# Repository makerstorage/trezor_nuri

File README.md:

# trezor_nuri
I slightly change the trezor one hw (https://github.com/trezor/trezor-hardware/tree/master/electronics/trezor_one) in order to solder the components easily. I use 0805 package components. This design can be more popular for the maker community. I also watch this video (https://www.youtube.com/watch?v=mZmv4wG6_PE) and do not use the resistors that are not populated also on the original trezor one. Unfortunately I can not make my design work :( 
I saw that all the voltage points have 3v. I am not expert but I try to upload the demo code and as well as the firmware as described here (https://mcudev.github.io/trezor-dev-kit/) I can upload the bin files without problem. The STlink v2 also finds the STM32 IC.
I am looking for help from the experts. I am here to try your all suggestions.

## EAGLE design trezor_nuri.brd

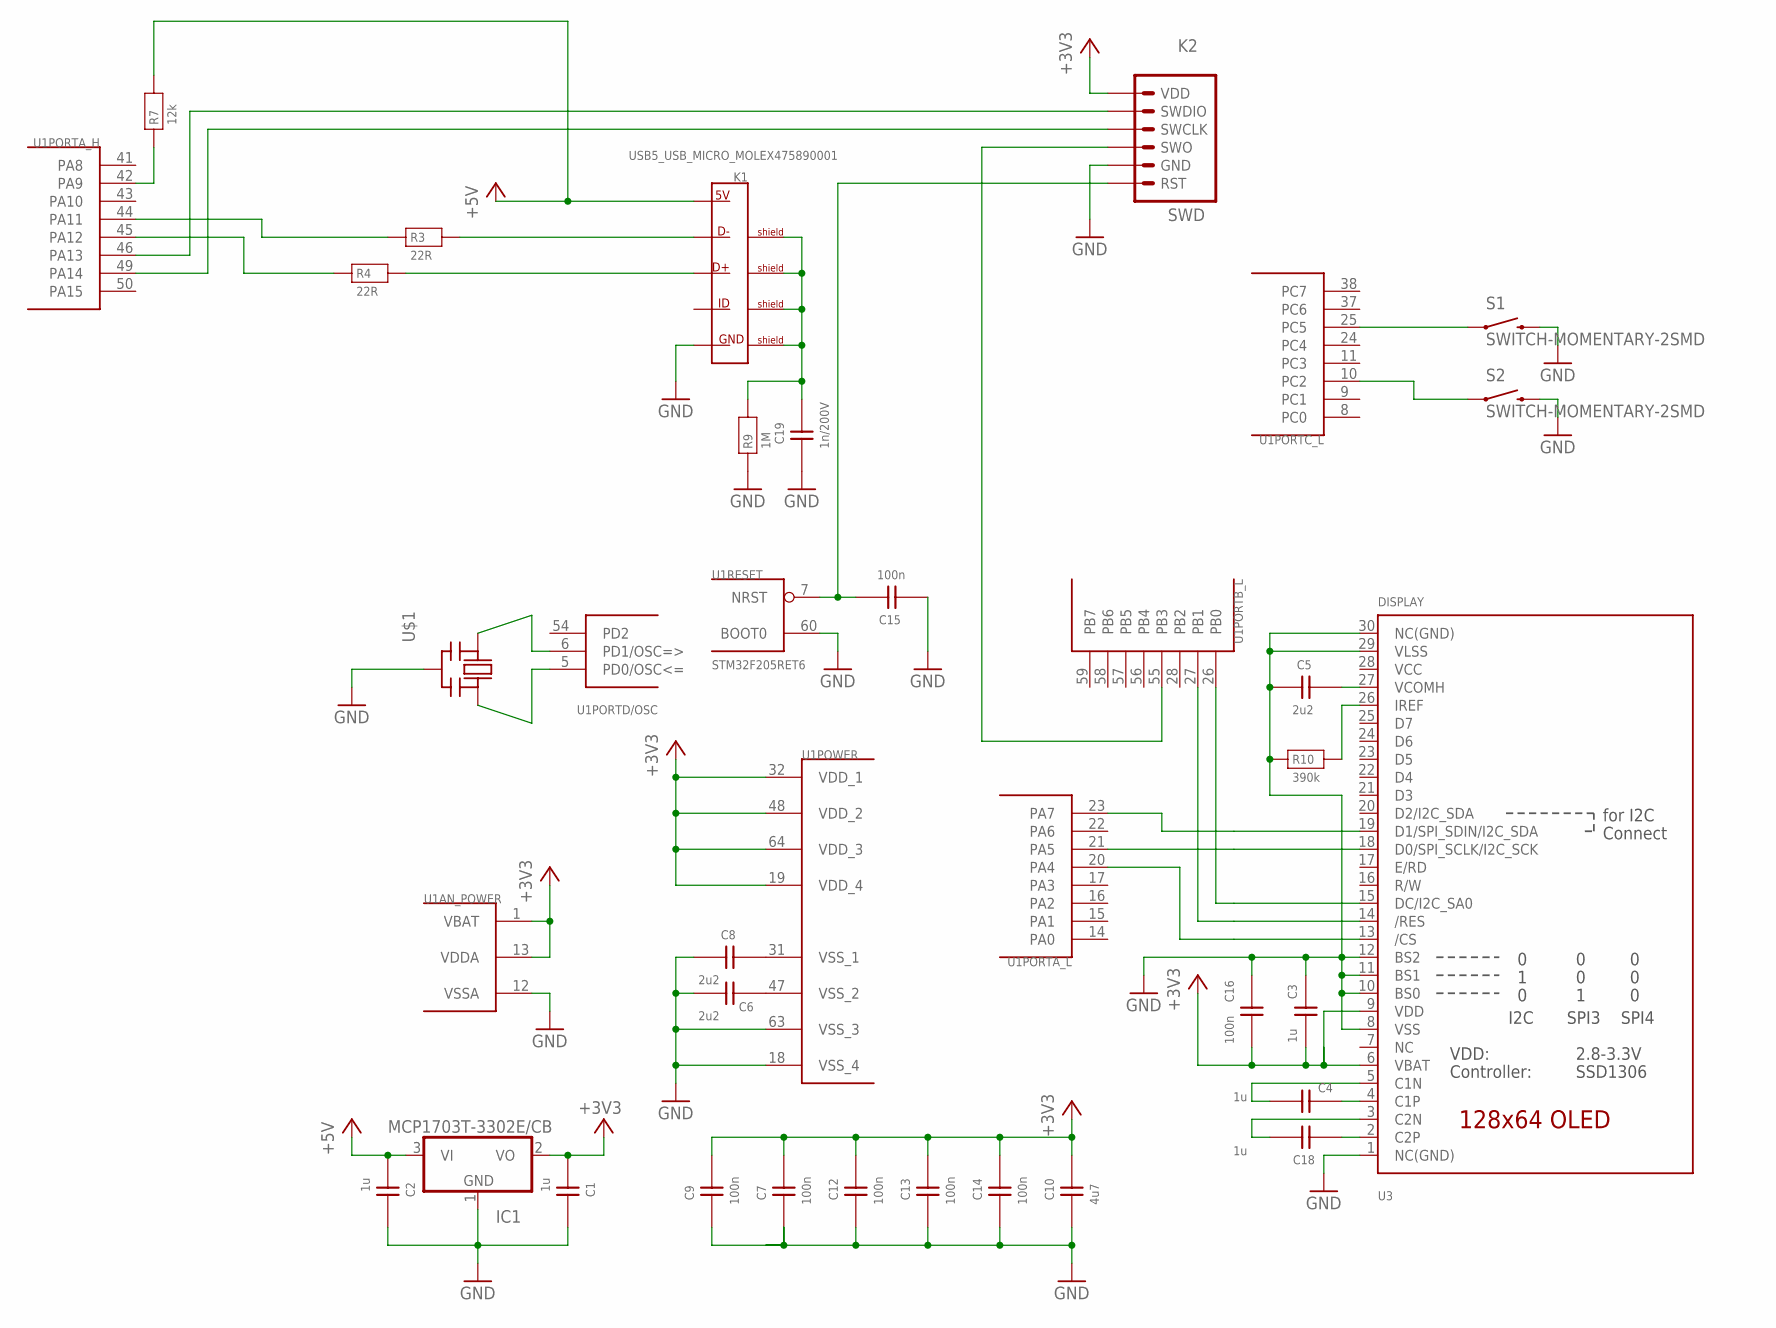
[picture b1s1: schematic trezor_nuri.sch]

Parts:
C1, C2, C3, C4, C18: 1u; 0805
C5, C6, C8: 2u2; 0805
C7, C9, C12, C13, C14, C15, C16: 100n; 0805
C10: 4u7; 0805
C19: 1n/200V; 0805
IC1: MCP1703T-3302E/CB; SOT23
K1: USB5_USB_MICRO_MOLEX475890001; USB_MICRO-MOLEX475890001
K2: SWD
R3, R4: 22R; 0805
R7: 12k; 0805
R9: 1M; 0805
R10: 390k; 0805
S1, S2: SWITCH-MOMENTARY-2SMD; TACTILE_SWITCH_SMD
U1: STM32F205RET6; TQFP64
U3: DISPLAY; UG-2864HSWEG01_0.96IN_WRAPAROUND
U$1: CERMOSCILL-CSTCRG; CSTCR-G

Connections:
+3V3: C1.1, C3.1, C7.2, C9.2, C10.2, C12.2, C13.2, C14.2, C16.1, IC1.2 (VO), K2.6 (VDD), U1.1 (VBAT), U1.13 (VDDA), U1.19 (VDD_4), U1.32 (VDD_1), U1.48 (VDD_2), U1.64 (VDD_3), U3.6 (VBAT), U3.9 (VDD)
+5V: C2.1, IC1.3 (VI), K1.1 (1_5V), R7.2
GND: C1.2, C2.2, C3.2, C5.1, C6.1, C7.1, C8.1, C9.1, C10.1, C12.1, C13.1, C14.1, C15.1, C16.2, C19.1, IC1.1 (GND), K1.5 (5_GND), K2.2 (GND), R9.1, R10.1, S1.3 (2), S1.4 (2), S2.3 (2), S2.4 (2), U1.12 (VSSA), U1.18 (VSS_4), U1.60 (BOOT0), U1.63 (VSS_3), U3.1 (NC(GND)), U3.8 (VSS), U3.10 (BS0), U3.11 (BS1), U3.12 (BS2), U3.29 (VLSS), U3.30 (NC(GND)), U$1.2 (GND)
unnamed: U1.23 (PA7), U3.19 (D1/SPI_SDIN/I2C_SDA)
unnamed: C15.2, K2.1 (RST), U1.7 (NRST)
unnamed: U1.26 (PB0), U3.15 (DC/I2C_SA0)
unnamed: C8.2, U1.31 (VSS_1)
unnamed: U1.21 (PA5), U3.18 (D0/SPI_SCLK/I2C_SCK)
unnamed: C5.2, U3.27 (VCOMH)
unnamed: U1.27 (PB1), U3.14 (/RES)
unnamed: C6.2, U1.47 (VSS_2)
unnamed: R10.2, U3.26 (IREF)
unnamed: C18.1, U3.2 (C2P)
unnamed: C4.1, U3.4 (C1P)
unnamed: C18.2, U3.3 (C2N)
unnamed: C4.2, U3.5 (C1N)
unnamed: K2.3 (SWO), U1.55 (PB3)
unnamed: K2.5 (SWDIO), U1.46 (PA13)
unnamed: U1.20 (PA4), U3.13 (/CS)
unnamed: K2.4 (SWCLK), U1.49 (PA14)
unnamed: R3.1, U1.44 (PA11)
unnamed: S1.1, S1.2 (1), U1.25 (PC5)
unnamed: S2.1, S2.2 (1), U1.10 (PC2)
unnamed: K1.2 (2_D-), R3.2
unnamed: K1.3 (3_D+), R4.2
unnamed: C19.2, K1.S1_BOT (SHIELD_1), K1.S1_TOP (SHIELD_1), K1.S2_BOT (SHIELD_2), K1.S2_TOP (SHIELD_2), K1.S3_BOT (SHIELD_3), K1.S3_TOP (SHIELD_3), K1.S4_BOT (SHIELD_4), K1.S4_TOP (SHIELD_4), K1.SA (SHIELD_1), K1.SB (SHIELD_2), R9.2
unnamed: R7.1, U1.42 (PA9)
USB_D_P: R4.1, U1.45 (PA12)
VCC: U3.28 (VCC)
XTAL1: U1.6 (PD1/OSC=>), U$1.1 (IN)
XTAL2: U1.5 (PD0/OSC<=), U$1.3 (OUT)

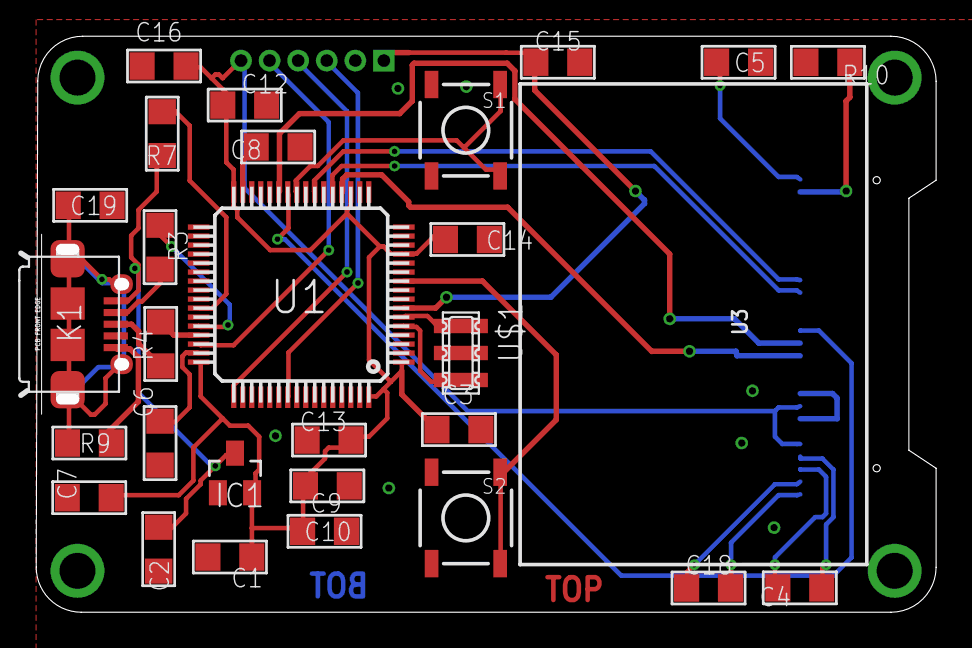
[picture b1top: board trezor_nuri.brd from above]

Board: 2 copper layers, 50.0 x 32.0 mm, 30 parts (0 on the bottom side), 30 nets.

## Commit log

2021-05-29 schematics pdf added

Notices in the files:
parts and their libraries:
microbuilder: This work is placed in the public domain, and may be freely used for commercial and non-commercial work with the following conditions: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
SparkFun-Electromechanical: Licensing: CC v3.0 Share-Alike You are welcome to use this library for commercial purposes.
